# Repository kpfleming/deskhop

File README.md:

#  DeskHop - Fast Desktop Switching
## JLCPCB version (see below)

Did you ever notice how, in the crazy world of tech, there's always that one quirky little project trying to solve a problem so niche that its only competitors might be a left-handed screwdriver and a self-hiding alarm clock?

I use two different computers in my daily workflow and share a single keyboard/mouse pair between them. Trying several USB switching boxes found on Amazon made me realize they all suffer from similar issues - it takes a while to switch, the process is quite clumsy when trying to find the button and frankly, it just doesn't get any better with time. 

All I wanted was a way to use a keyboard shortcut to quickly switch outputs, paired with the ability to do the same by magically moving the mouse pointer between monitors. This project enables you to do both, even if your computers run different operating systems!

## Features

- Completely **free and open source**
- No noticeable delay when switching
- Simply drag the mouse pointer between computers
- No software installed
- Affordable and obtainable components (<15€)
- 3D printable snap-fit case
- Full Galvanic isolation between your outputs
- Works with Linux, macOS and Windows

------

## How it works

The device acts as an intermediary between your keyboard/mouse and the computer, establishing and maintaining connections with both computers at once. Then it chooses where to forward your mouse and keystrokes to, depending on your selection. Keyboard follows the mouse and vice versa, so just dragging the mouse to the other desktop will switch both.

## Mouse 

To get the mouse cursor to magically jump across, the mouse hid report descriptor was changed to use absolute coordinates and then the mouse reports (that still come in relative movements) accumulate internally, keeping the accurate tally on the position. 

When you try to leave the monitor area in the direction of the other monitor, it keeps the Y coordinate and swaps the maximum X for a minimum X, then flips the outputs. This ensures that the cursor seamlessly appears at the same height on the other monitor, enhancing the perception of a smooth transition.

 <p align="center"> Dragging the mouse from Mac to Linux automatically switches outputs. 
 </p>

-----
 
The actual switch happens at the very moment when one arrow stops moving and the other one starts.

## Keyboard

Acting as a USB Host and querying your keyboard periodically, it looks for a preconfigured hotkey in the hid report (usually Caps Lock for me). When found, it will forward all subsequent characters to the other output.

To have a visual indication which output you are using at any given moment, you can repurpose keyboard LEDs and have them provide the necessary feedback. 

It also remembers the LED state for each computer, so you can pick up exactly how you left it. 

## How to build

```
PICO_BOARD=pico PICO_SDK_PATH=/your/sdk/path cmake -S . -B build
cmake --build build
```

## Using pre-built images

Alternatively, you can use the [pre-built images](binaries/). Take the Pico board that goes to slot A on the PCB and hold the on-board button while connecting the cable.

It should appear as a USB drive on your system. Copy the corresponding board_A.uf2 file there and repeat the same with B.

## Upgrading firmware

Option 1 - Open the case, hold the button while connecting each Pico and copy the right uf2 to it.

Option 2 - Switch a board to BOOTSEL mode by using a special key combination (listed below). 

This will make the corresponding Pico board enter the bootloader upgrade mode and act as USB flash drive. Now you can drag-and-drop the .uf2 file to it (you might need to plug in your mouse directly).

## Misc features

### Mouse slowdown

Ever tried to move that YT video slider to a specific position but your mouse moves too jumpy and suddenly you are moving your hand super-carefully like you're 5 and playing "Operation" all over again?

**Press right CTRL + right ALT** to toggle a slow-mouse mode. The mouse pointer will slow down considerably, enabling you to get the finer precision work done and still have your mouse moving normally by quickly pressing the same keys again.

### Switch Lock

If you want to lock yourself to one screen, use ```RIGHT CTRL + L```.
This will make sure you won't accidentally leave your current screen. To turn off, press the same key combo again.

### Screensaver

Supposedly built in to prevent computer from entering standby, but truth be told - it is just fun to watch. Off by default, will make your mouse pointer bounce around the screen like a Pong ball. When enabled, it activates after a period of inactivity defined in user config header and automatically switches off as soon as you send any output towards that screen. 

## Hardware

[The circuit](schematics/DeskHop.pdf) is based on two Raspberry Pi Pico boards, chosen because they are cheap (4.10 € / pc), can be hand soldered and most suppliers have them in stock.

The Picos are connected using UART and separated by an Analog Devices ADuM1201 dual-channel digital isolator (~3€). 

While they normally don't have support for dual USB, thanks to an [amazing project](https://github.com/sekigon-gonnoc/Pico-PIO-USB) where USB is implemented using the programmable IO wizardry found in RP2040, there is support for it to act both as an USB host and device.  

## PCB

To keep things as simple as possible for DIY builds, the traces were kept on one side and the number of parts kept to a theoretical minimum.

USB D+/D- differential lines should be identical in length, but they are slightly asymmetrical on purpose to counter the length difference on the corresponding GPIO traces PICO PCB itself, so the overall lengths should match.

Zd (differential impedance) is aimed as 90 ohm (managed to get ~107, close enough :)).

The thickness is designed to be 1.6 mm for snap-fit to work as expected.

Planned changes:
- Add 15 ohm resistors for D+ / D- lines
- Add decoupling capacitance near VBUS line on USB-A connector (~100 uF)
- Add an ESD protection device near the USB connector
- Add indications on the silkscreen for pin1 on the ADuM1201
- Add indications on the silkscreen for which Raspberry Pi Pico pins need to be soldered

... done, waiting on PCBs to re-test and verify everything. Stay tuned for an updated version!

## Case

Since I'm not very good with 3d, the case is [simple and basic](case/) but does the job. It should be easy to print, uses ~33g of filament and takes a couple of hours.

Horizontal PCB movements are countered by pegs sliding through holes and vertical movements by snap-fit lugs on the side - no screws required.

Micro USB connectors on both boards are offset from the side of the case, so slightly larger holes should allow for cables to reach in. 

The lid is of a snap-fit design, with a screwdriver slot for opening. The markings on top are recessed and can be finished with e.g. crayons to give better contrast (or simply left as-is).

## Bill of materials

Note that this fork of the project has been converted to use parts
from [LCSC](https://www.lcsc.com/), specifically parts that are kept
in stock at JLCPCB. This reduces costs and shortens assembly times,
but is only useful if you plan on ordering fully-assembled boards from
JLCPCB.

Prices quoted below are from a qty 10 unit order on 2024-02-26.

| Component          | Qty | LCSC SKU | Unit Price / $ | Price / $|
|--------------------|-----|----------|----------------|----------|
| Raspberry Pi Pico  | 2   | C7203002 | 5.93           | 11.85    |
| ISO7721DRRZ        | 1   | C366164  | 0.56           |  0.56    |
| Cap 1206 SMD 100nF | 2   | C2858367 | 0.013          |  0.03    |
| USB-A PCB conn.    | 2   | C42411   | 0.049          |  0.10    |
| Headers 2.54 1x03  | 2   | C2915006 | 0.176          |  0.35    |
|                    |     |          |                |          |
|                    |     |          |          Total | 12.89    |

Additional steps:

 - making the PCB ([Gerber provided](pcb/), choose 1.6 mm thickness)
 - 3d printing the case ([stl files provided](case/), ~33g filament)

## Assembly guide

If you have some experience with electronics, you don't need this. However, some of you might not, and in that case this video might help guide you through the process. Please note, after soldering you should clean the flux from the PCB to prevent corrosion. 

The standard process to do that is using isopropyl alcohol and an old toothbrush. But guess what? I'm not putting my old toothbrush online, so you'll just have to improvise that part :)

## Usage guide

### Keyboard shortcuts

_Firmware upgrade_
- ```Right Shift + F12 + Left Shift + A``` - put board A in FW upgrade mode
- ```Right Shift + F12 + Left Shift + B``` - put board B in FW upgrade mode

_Usage_
- ```Right CTRL + Right ALT``` - Toggle slower mouse mode
- ```Right CTRL + L``` - Lock/Unlock mouse desktop switching
- ```Caps Lock``` - Switch between outputs

_Config_
- ```Right Shift + F12 + D``` - remove flash config
- ```Right Shift + F12 + Y``` - save screen switch offset
- ```Right Shift + F12 + S``` - turn on/off screensaver option

### Switch cursor height calibration

This step is not required, but it can be handy if your screens are not perfectly aligned or differ in size. The objective is to have the mouse pointer come out at exactly the same height.

Just park your mouse on the LARGER screen at the height of the smaller/lower screen (illustrated) and press ```Right Shift + F12 + Y```. Your LED (and caps lock) should flash in confirmation.

Repeat for the bottom border (if it's above the larger screen's border). This will get saved to flash and it should keep this calibration value from now on.

### Other configuration

Mouse speed can now be configured per output screen and per axis. If you have multiple displays under Linux, your X speed is probably too fast, so you need to configure it in user_config.h and rebuild. In the future, this will be configurable without having to do that.

### Functional verification

When you connect a new USB peripheral, the board will flash the led twice, and instruct the other board to do the same. This way you can test if USB and outgoing communication works for each board.

Do this test by first plugging the keyboard on one side and then on the other. If everything is OK, leds will flash quickly back and forth in both cases.

## Security and Safety

Some features are missing on purpose, despite the fact it would make the device easier to use or simpler to configure. Here is a quick breakdown of these decisions:

- There is no copy-paste or *any* information sharing between systems. This prevents information leakage.
- No webhid device management or any inbound connectivity from the output computers, with the only exception of standard keyboard LED on/off messages, hard limited to 1 byte of data.
- No FW upgrade triggering from the outputs. Only explicit and deliberate user action through a special keyboard shortcut may do that.
- No plugged-in keyboard/mouse custom endpoints are exposed or information forwarded towards these devices. Their potential vulnerabilities are effectively firewalled from the computer.
- No input history is allowed to be retained.
- Outputs are physically separated and galvanically isolated with a minimal isolation voltage of 2kV.
- All packets exchanged between devices are of fixed length, no code is transferred and no raw config exchange of any kind can take place.
- There is no bluetooth or wifi, networking, Internet access, usb drives etc.
- No connected computer is considered trusted under any circumstances.
- Entirety of the code is open source, without any binary blobs and thoroughly commented to explain its purpose. I encourage you to never trust anyone and always make sure you know what you are running by doing a manual audit.

This still doesn't guarantee anything, but I believe it makes a reasonable set of ground rules to keep you safe and protected.

## FAQ

1. I just have two Picos, can I do without a PCB and isolator?

*Sure. Having an isolator is recommended but it should work without it.*

2. What happens if I have two different resolutions on my monitors?

*The mouse movement is done in abstract coordinate space and your computer figures out how that corresponds with the physical screen, so it should just work.*

3. Where can I buy it?

*I'm not selling anything, this is just a personal, non-commercial hobby project.*

*[update] There is a manufacturing/assembly company in China that might offer PCBs in qty of 1, assembled boards and boards + case, so stay tuned.*

*I **don't want to take any commission** on this - the only goal is to provide an alternative for people who don't feel confident enough to assemble the boards themselves.*

4. When the active screen is changed via the mouse, does the keyboard follow (and vice versa)?

*Yes, the idea was to make it behave like it was one single computer.*

5. Will this work with keyboard/mouse combo dongles, like the Logitech Unifying receiver?

*Not tested yet, but the latest version might actually work (please provide feedback).*

6. Will this work with wireless mice and keyboards that have separate wireless receivers (one for the mouse, another for the keyboard)?

*It should work - tried an Anker wireless mouse with a separate receiver and that worked just fine.*

7. I have issues with build or compilation

*Check out the [Troubleshooting Wiki](https://github.com/hrvach/deskhop/wiki/Troubleshooting) that might have some answers.*

## Software Alternatives

There are several software alternatives you can use if that works in your particular situation.

1. [Barrier](https://github.com/debauchee/barrier) - Free, Open Source
2. [Input Leap](https://github.com/input-leap/input-leap) - Free, Open Source
3. [Synergy](https://symless.com/synergy) - Commercial
4. [Mouse Without Borders](https://www.microsoft.com/en-us/garage/wall-of-fame/mouse-without-borders/) - Free, Windows only
5. [Universal Control](https://support.apple.com/en-my/HT212757) - Free, Apple thing

## Shortcomings

- Windows 10 broke HID absolute coordinates behavior in KB5003637, so you can't use more than 1 screen on Windows (mouse will stay on the main screen).
- Code needs cleanup, some refactoring etc.
- Occasional bugs and weird behavior.
- Not tested with a wide variety of devices, I don't know how it will work with your hardware. There is a reasonable chance things might not work out-of-the-box. 
- Advanced keyboards (with knobs, extra buttons or sliders) will probably face issues where this additional hardware doesn't work.
- Super-modern mice with 300 buttons might see some buttons not work as expected.
- NOTE: Both computers need to be connected and provide power to the USB for this to work (as each board gets powered by the computer it plugs into). Many desktops and laptops will provide power even when shut down nowadays. If you need to run with one board fully disconnected, you should be able to use a USB hub to plug both keyboard and mouse to a single port.

## Progress

So, what's the deal with all the enthusiasm? I can't believe it - please allow me to thank you all! I've never expected this kind of interest in a simple personal project, so the initial features are pretty basic (just like my cooking skills) and mostly cover my own usecase. Stay tuned for firmware updates that should bring wider device compatibility, more features and less bugs. As this is a hobby project, I appreciate your understanding for being time-constrained and promise to do the best I can.

Planned features:
- ~~Proper TinyUSB host integration~~ (done)
- ~~HID report protocol parsing, not just boot protocol~~ (mostly done)
- ~~Support for unified dongle receivers~~
- ~~Support for USB hubs and single-sided operation~~
- Configurable screens (partially)
- ~~Permament configuration stored in flash~~
- Better support for keyboards with knobs and mice with mickeys
- Unified firmware for both Picos
- ... and more!

Working on a *lite* version which provides basic functionality with just a single Pico W board, lowering the cost even further and enabling you to try it out even with no added hardware or PCB.

Mouse polling should now work at 1000 Hz (the dips in the graph is my arm hurting from all the movement :-)):

## Disclaimer

I kindly request that anyone attempting to build this project understands and acknowledges that I am not liable for any injuries, damages, or other consequences. Your safety is important, and I encourage you to approach this project carefully, taking necessary precautions and assuming personal responsibility for your well-being throughout the process. Please don't get electrocuted, burned, stressed or angry. Have fun and enjoy! 

Happy switchin'!

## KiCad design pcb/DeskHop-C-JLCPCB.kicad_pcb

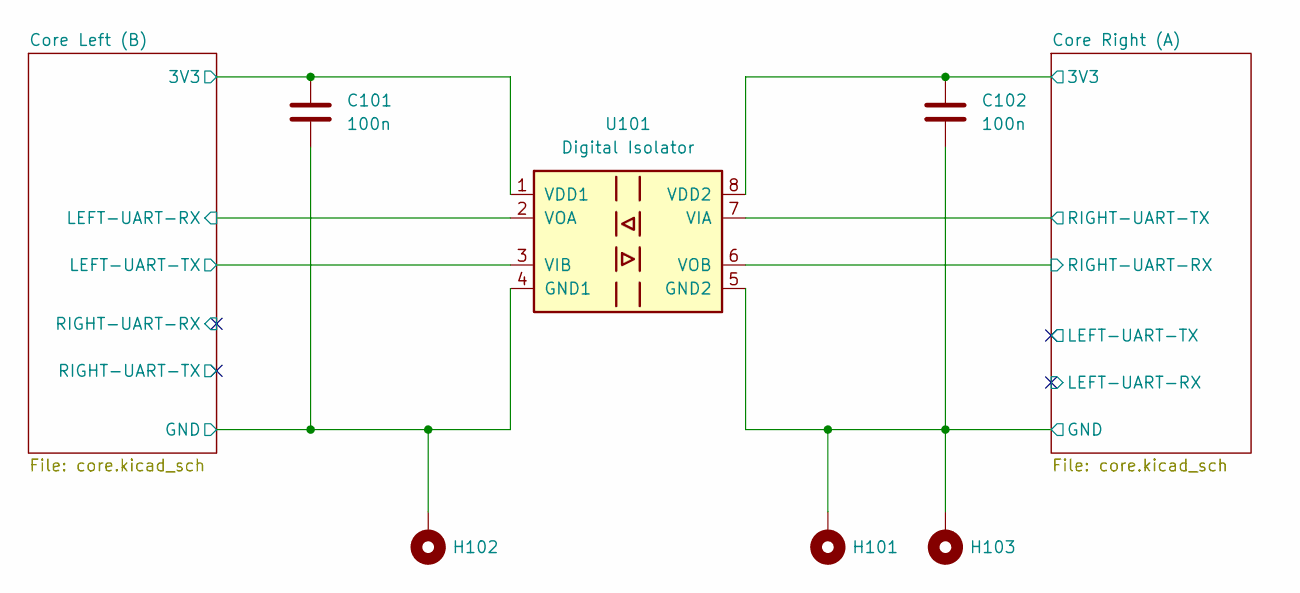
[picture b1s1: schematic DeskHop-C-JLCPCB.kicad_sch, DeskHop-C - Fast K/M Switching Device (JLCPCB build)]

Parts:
C101, C102: 100n; C_0402_1005Metric; MPN CC0402KRX5R5BB104; LCSC C541405
H101, H102, H103: MountingHole_Pad; MountingHole_2.7mm_M2.5_Pad_Via
U101: Digital Isolator; SOIC-8_3.9x4.9mm_P1.27mm; MPN ISO7721DR; LCSC C366164

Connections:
/Core Left (B)/3V3: C101.1, U101.1 (VDD1); also elsewhere on the board
/Core Left (B)/GND: C101.2, H102.1, U101.4 (GND1); also elsewhere on the board
/Core Left (B)/LEFT-UART-RX: U101.2 (VOA); also elsewhere on the board
/Core Left (B)/LEFT-UART-TX: U101.3 (VIB); also elsewhere on the board
/Core Right (A)/3V3: C102.1, U101.8 (VDD2); also elsewhere on the board
/Core Right (A)/GND: C102.2, H101.1, H103.1, U101.5 (GND2); also elsewhere on the board
/Core Right (A)/RIGHT-UART-RX: U101.6 (VOB); also elsewhere on the board
/Core Right (A)/RIGHT-UART-TX: U101.7 (VIA); also elsewhere on the board

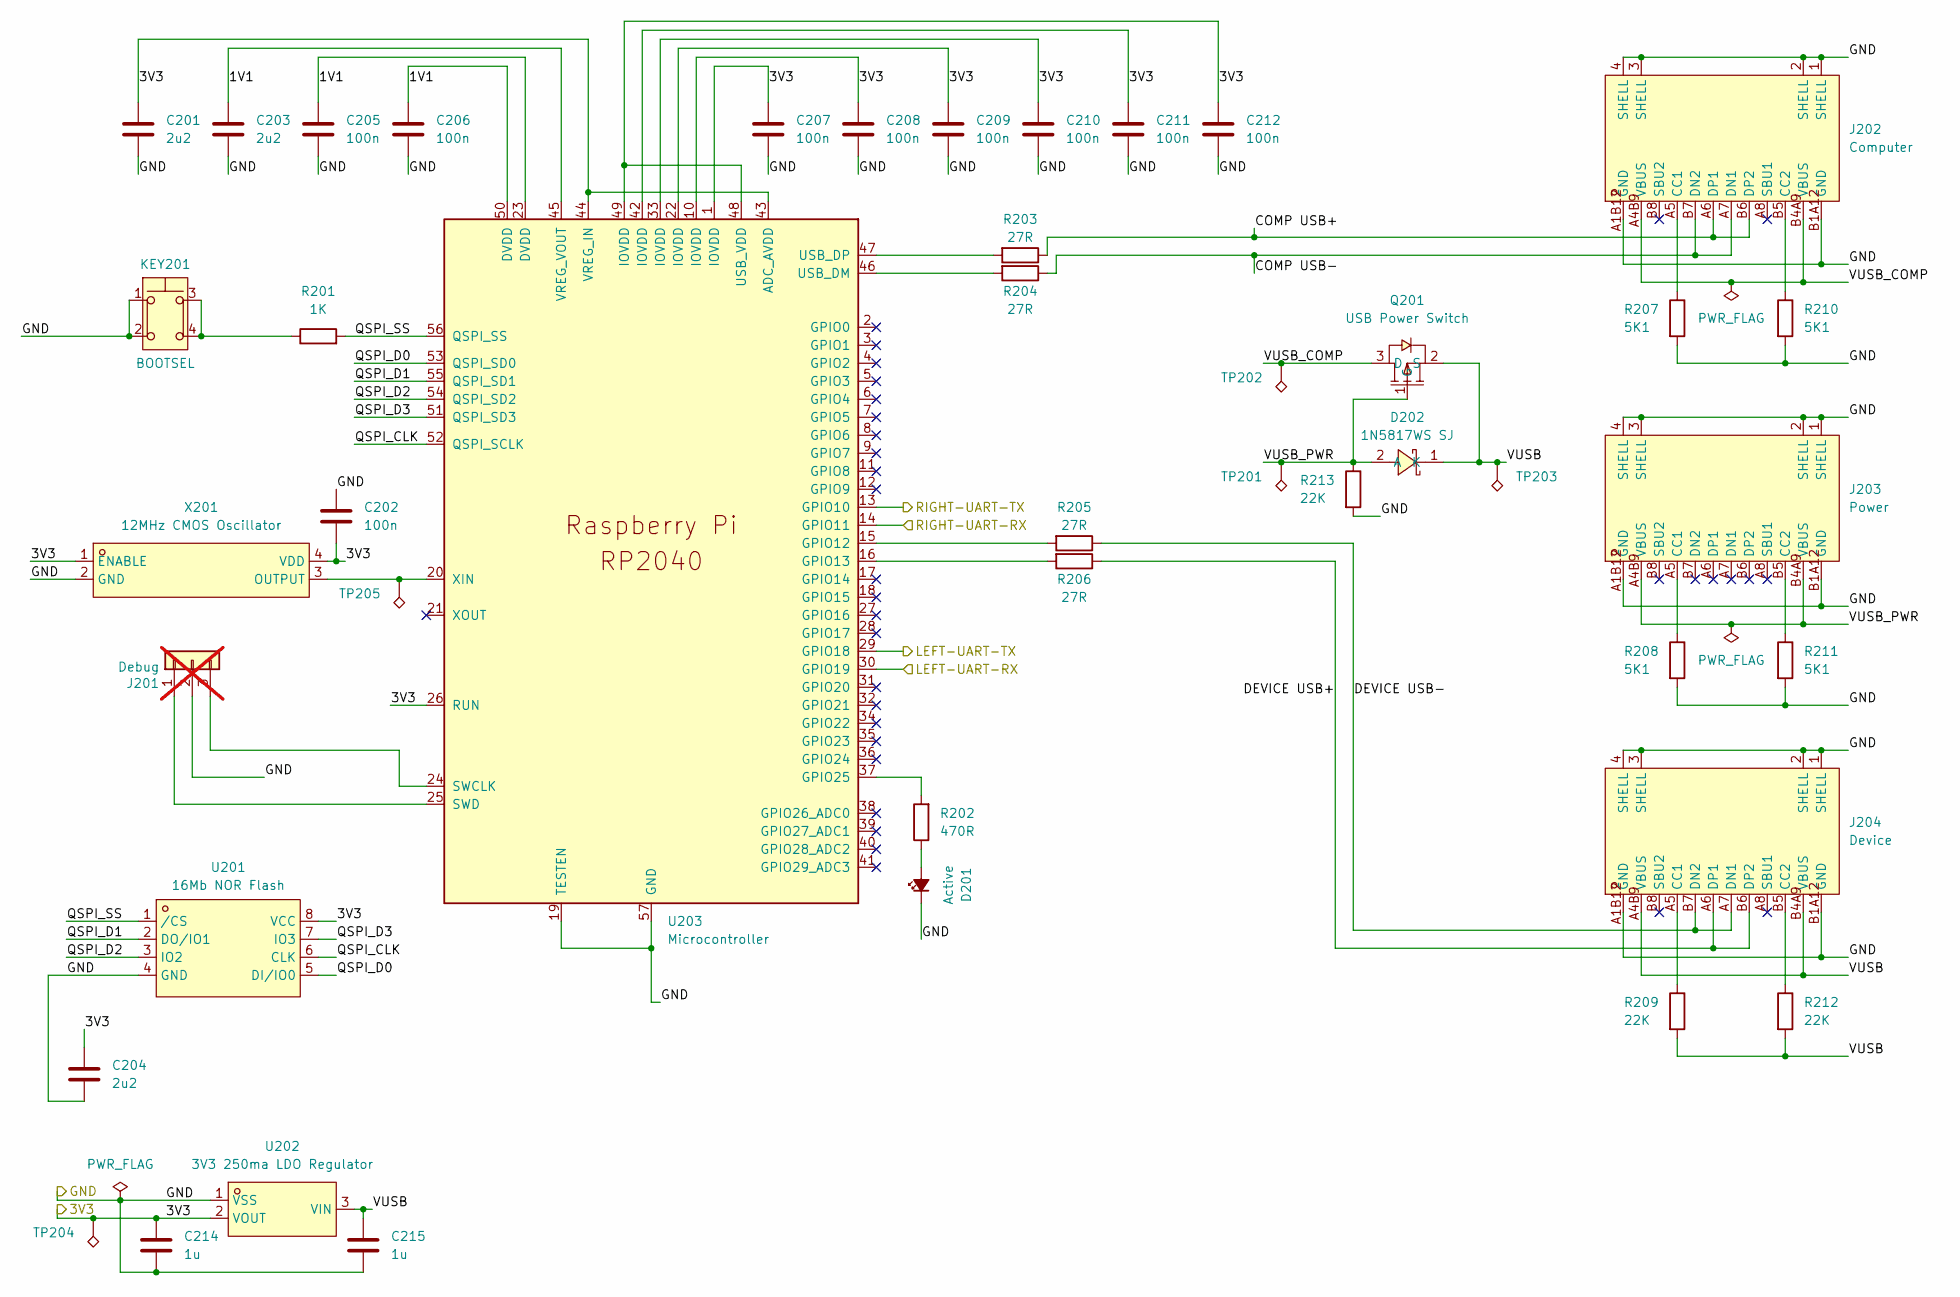
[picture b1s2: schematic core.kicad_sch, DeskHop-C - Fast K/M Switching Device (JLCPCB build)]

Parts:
C201, C203, C204: 2u2; C_0402_1005Metric; MPN CC0402KRX5R5BB225; LCSC C541409
C202, C205, C206, C207, C208, C209, C210, C211, C212: 100n; C_0402_1005Metric; MPN CC0402KRX5R5BB104; LCSC C541405
C214, C215: 1u; C_0402_1005Metric; MPN CC0402KRX5R5BB105; LCSC C106253
D201: Active; LED_0603_1608Metric; MPN NCD0805B2APG1608CGKC/T; LCSC C5875737
D202: 1N5817WS SJ; SOD-323_L1.7-W1.3-LS2.6-RD-1; MPN 1N5817WS; LCSC C2828424
J201: Debug; PinHeader_1x03_P2.54mm_Vertical; not fitted
J202: Computer; USB-C-SMD_G-SWITCH_GT-USB-7010ASV; MPN GT-USB-7010ASV; LCSC C2988369
J203: Power; USB-C-SMD_G-SWITCH_GT-USB-7010ASV; MPN GT-USB-7010ASV; LCSC C2988369
J204: Device; USB-C-SMD_G-SWITCH_GT-USB-7010ASV; MPN GT-USB-7010ASV; LCSC C2988369
KEY201: BOOTSEL; KEY-SMD_4P-L4.2-W3.2-P2.20-LS4.6; MPN SKRPASE010; LCSC C470427
Q201: USB Power Switch; SOT-23-3_L2.9-W1.3-P0.95-LS2.4-BR-1; MPN DMG2305UX; LCSC C2940629
R201: 1K; R_0402_1005Metric; MPN AC0402FR-071KL; LCSC C144789
R202: 470R; R_0402_1005Metric; MPN AC0402FR-07470RL; LCSC C227095
R203, R204, R205, R206: 27R; R_0402_1005Metric; MPN RC0402FR-0727RL; LCSC C138021
R207, R208, R210, R211: 5K1; R_0402_1005Metric; MPN AC0402FR-075K1L; LCSC C144745
R209, R212, R213: 22K; R_0402_1005Metric; MPN AC0402FR-0722KL; LCSC C144778
TP201, TP202, TP203, TP204, TP205: TestPoint_Alt; TestPoint_Pad_1.0x1.0mm
U201: 16Mb NOR Flash; SOIC-8_L5.3-W5.3-P1.27-LS8.0-BL; MPN W25Q16JVSSIQ; LCSC C82317
U202: 3V3 250ma LDO Regulator; SOT-23-3_L3.0-W1.7-P0.95-LS2.9-BR; MPN XC6206P332MR; LCSC C347376
U203: Microcontroller; RP2040-QFN-56; MPN RP2040; LCSC C2040
X201: 12MHz CMOS Oscillator; OSC-SMD_4P-L3.2-W2.5-BL-1; MPN S3D12.000000B20F30T; LCSC C387348

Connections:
/Core Left (B)/1V1: C203.2, C205.2, C206.2, U203.23 (DVDD), U203.45 (VREG_VOUT), U203.50 (DVDD)
/Core Left (B)/3V3: C201.2, C202.1, C204.1, C207.2, C208.2, C209.2, C210.2, C211.2, C212.2, C214.1, TP204.1, U201.8 (VCC), U202.2 (VOUT), U203.1 (IOVDD), U203.10 (IOVDD), U203.22 (IOVDD), U203.26 (RUN), U203.33 (IOVDD), U203.42 (IOVDD), U203.43 (ADC_AVDD), U203.44 (VREG_IN), U203.48 (USB_VDD), U203.49 (IOVDD), X201.1 (ENABLE), X201.4 (VDD); also elsewhere on the board
/Core Left (B)/COMP USB+: J202.A6 (DP1), J202.B6 (DP2), R203.1
/Core Left (B)/COMP USB-: J202.A7 (DN1), J202.B7 (DN2), R204.1
/Core Left (B)/DEVICE USB+: J204.A6 (DP1), J204.B6 (DP2), R205.1
/Core Left (B)/DEVICE USB-: J204.A7 (DN1), J204.B7 (DN2), R206.1
/Core Left (B)/GND: C201.1, C202.2, C203.1, C204.2, C205.1, C206.1, C207.1, C208.1, C209.1, C210.1, C211.1, C212.1, C214.2, C215.2, D201.1 (K), J201.2, J202.1 (SHELL), J202.2 (SHELL), J202.3 (SHELL), J202.4 (SHELL), J202.A1B12 (GND), J202.B1A12 (GND), J203.1 (SHELL), J203.2 (SHELL), J203.3 (SHELL), J203.4 (SHELL), J203.A1B12 (GND), J203.B1A12 (GND), J204.1 (SHELL), J204.2 (SHELL), J204.3 (SHELL), J204.4 (SHELL), J204.A1B12 (GND), J204.B1A12 (GND), KEY201.1, KEY201.2, R207.2, R208.2, R210.2, R211.2, R213.2, U201.4 (GND), U202.1 (VSS), U203.19 (TESTEN), U203.57 (GND), X201.2 (GND); also elsewhere on the board
/Core Left (B)/LEFT-UART-RX: U203.30 (GPIO19); also elsewhere on the board
/Core Left (B)/LEFT-UART-TX: U203.29 (GPIO18); also elsewhere on the board
/Core Left (B)/QSPI_CLK: U201.6 (CLK), U203.52 (QSPI_SCLK)
/Core Left (B)/QSPI_D0: U201.5 (DI/IO0), U203.53 (QSPI_SD0)
/Core Left (B)/QSPI_D1: U201.2 (DO/IO1), U203.55 (QSPI_SD1)
/Core Left (B)/QSPI_D2: U201.3 (IO2), U203.54 (QSPI_SD2)
/Core Left (B)/QSPI_D3: U201.7 (IO3), U203.51 (QSPI_SD3)
/Core Left (B)/QSPI_SS: R201.2, U201.1 (/CS), U203.56 (QSPI_SS)
/Core Left (B)/RIGHT-UART-RX: U203.14 (GPIO11)
/Core Left (B)/RIGHT-UART-TX: U203.13 (GPIO10)
/Core Left (B)/VUSB: C215.1, D202.1 (K), J204.A4B9 (VBUS), J204.B4A9 (VBUS), Q201.2 (S), R209.2, R212.2, TP203.1, U202.3 (VIN)
/Core Left (B)/VUSB_COMP: J202.A4B9 (VBUS), J202.B4A9 (VBUS), Q201.3 (D), TP202.1
/Core Left (B)/VUSB_PWR: D202.2 (A), J203.A4B9 (VBUS), J203.B4A9 (VBUS), Q201.1 (G), R213.1, TP201.1
unnamed: D201.2 (A), R202.1
unnamed: J201.1, U203.25 (SWD)
unnamed: J201.3, U203.24 (SWCLK)
unnamed: J202.A5 (CC1), R207.1
unnamed: J202.B5 (CC2), R210.1
unnamed: J203.A5 (CC1), R208.1
unnamed: J203.B5 (CC2), R211.1
unnamed: J204.A5 (CC1), R209.1
unnamed: J204.B5 (CC2), R212.1
unnamed: KEY201.3, KEY201.4, R201.1
unnamed: R206.2, U203.15 (GPIO12)
unnamed: R205.2, U203.16 (GPIO13)
unnamed: R202.2, U203.37 (GPIO25)
unnamed: R204.2, U203.46 (USB_DM)
unnamed: R203.2, U203.47 (USB_DP)
unnamed: TP205.1, U203.20 (XIN), X201.3 (OUTPUT)

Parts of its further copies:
C301, C303, C304: 2u2; C_0402_1005Metric; MPN CC0402KRX5R5BB225; LCSC C541409
C302, C305, C306, C307, C308, C309, C310, C311, C312: 100n; C_0402_1005Metric; MPN CC0402KRX5R5BB104; LCSC C541405
C314, C315: 1u; C_0402_1005Metric; MPN CC0402KRX5R5BB105; LCSC C106253
D301: Active; LED_0603_1608Metric; MPN NCD0805B2APG1608CGKC/T; LCSC C5875737
D302: 1N5817WS SJ; SOD-323_L1.7-W1.3-LS2.6-RD-1; MPN 1N5817WS; LCSC C2828424
J301: Debug; PinHeader_1x03_P2.54mm_Vertical; not fitted
J302: Computer; USB-C-SMD_G-SWITCH_GT-USB-7010ASV; MPN GT-USB-7010ASV; LCSC C2988369
J303: Power; USB-C-SMD_G-SWITCH_GT-USB-7010ASV; MPN GT-USB-7010ASV; LCSC C2988369
J304: Device; USB-C-SMD_G-SWITCH_GT-USB-7010ASV; MPN GT-USB-7010ASV; LCSC C2988369
KEY301: BOOTSEL; KEY-SMD_4P-L4.2-W3.2-P2.20-LS4.6; MPN SKRPASE010; LCSC C470427
Q301: USB Power Switch; SOT-23-3_L2.9-W1.3-P0.95-LS2.4-BR-1; MPN DMG2305UX; LCSC C2940629
R301: 1K; R_0402_1005Metric; MPN AC0402FR-071KL; LCSC C144789
R302: 470R; R_0402_1005Metric; MPN AC0402FR-07470RL; LCSC C227095
R303, R304, R305, R306: 27R; R_0402_1005Metric; MPN RC0402FR-0727RL; LCSC C138021
R307, R308, R310, R311: 5K1; R_0402_1005Metric; MPN AC0402FR-075K1L; LCSC C144745
R309, R312, R313: 22K; R_0402_1005Metric; MPN AC0402FR-0722KL; LCSC C144778
TP301, TP302, TP303, TP304, TP305: TestPoint_Alt; TestPoint_Pad_1.0x1.0mm
U301: 16Mb NOR Flash; SOIC-8_L5.3-W5.3-P1.27-LS8.0-BL; MPN W25Q16JVSSIQ; LCSC C82317
U302: 3V3 250ma LDO Regulator; SOT-23-3_L3.0-W1.7-P0.95-LS2.9-BR; MPN XC6206P332MR; LCSC C347376
U303: Microcontroller; RP2040-QFN-56; MPN RP2040; LCSC C2040
X301: 12MHz CMOS Oscillator; OSC-SMD_4P-L3.2-W2.5-BL-1; MPN S3D12.000000B20F30T; LCSC C387348

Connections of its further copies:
/Core Right (A)/1V1: C303.2, C305.2, C306.2, U303.23 (DVDD), U303.45 (VREG_VOUT), U303.50 (DVDD)
/Core Right (A)/3V3: C301.2, C302.1, C304.1, C307.2, C308.2, C309.2, C310.2, C311.2, C312.2, C314.1, TP304.1, U301.8 (VCC), U302.2 (VOUT), U303.1 (IOVDD), U303.10 (IOVDD), U303.22 (IOVDD), U303.26 (RUN), U303.33 (IOVDD), U303.42 (IOVDD), U303.43 (ADC_AVDD), U303.44 (VREG_IN), U303.48 (USB_VDD), U303.49 (IOVDD), X301.1 (ENABLE), X301.4 (VDD); also elsewhere on the board
/Core Right (A)/COMP USB+: J302.A6 (DP1), J302.B6 (DP2), R303.1
/Core Right (A)/COMP USB-: J302.A7 (DN1), J302.B7 (DN2), R304.1
/Core Right (A)/DEVICE USB+: J304.A6 (DP1), J304.B6 (DP2), R305.1
/Core Right (A)/DEVICE USB-: J304.A7 (DN1), J304.B7 (DN2), R306.1
/Core Right (A)/GND: C301.1, C302.2, C303.1, C304.2, C305.1, C306.1, C307.1, C308.1, C309.1, C310.1, C311.1, C312.1, C314.2, C315.2, D301.1 (K), J301.2, J302.1 (SHELL), J302.2 (SHELL), J302.3 (SHELL), J302.4 (SHELL), J302.A1B12 (GND), J302.B1A12 (GND), J303.1 (SHELL), J303.2 (SHELL), J303.3 (SHELL), J303.4 (SHELL), J303.A1B12 (GND), J303.B1A12 (GND), J304.1 (SHELL), J304.2 (SHELL), J304.3 (SHELL), J304.4 (SHELL), J304.A1B12 (GND), J304.B1A12 (GND), KEY301.1, KEY301.2, R307.2, R308.2, R310.2, R311.2, R313.2, U301.4 (GND), U302.1 (VSS), U303.19 (TESTEN), U303.57 (GND), X301.2 (GND); also elsewhere on the board
/Core Right (A)/LEFT-UART-RX: U303.30 (GPIO19)
/Core Right (A)/LEFT-UART-TX: U303.29 (GPIO18)
/Core Right (A)/QSPI_CLK: U301.6 (CLK), U303.52 (QSPI_SCLK)
/Core Right (A)/QSPI_D0: U301.5 (DI/IO0), U303.53 (QSPI_SD0)
/Core Right (A)/QSPI_D1: U301.2 (DO/IO1), U303.55 (QSPI_SD1)
/Core Right (A)/QSPI_D2: U301.3 (IO2), U303.54 (QSPI_SD2)
/Core Right (A)/QSPI_D3: U301.7 (IO3), U303.51 (QSPI_SD3)
/Core Right (A)/QSPI_SS: R301.2, U301.1 (/CS), U303.56 (QSPI_SS)
/Core Right (A)/RIGHT-UART-RX: U303.14 (GPIO11); also elsewhere on the board
/Core Right (A)/RIGHT-UART-TX: U303.13 (GPIO10); also elsewhere on the board
/Core Right (A)/VUSB: C315.1, D302.1 (K), J304.A4B9 (VBUS), J304.B4A9 (VBUS), Q301.2 (S), R309.2, R312.2, TP303.1, U302.3 (VIN)
/Core Right (A)/VUSB_COMP: J302.A4B9 (VBUS), J302.B4A9 (VBUS), Q301.3 (D), TP302.1
/Core Right (A)/VUSB_PWR: D302.2 (A), J303.A4B9 (VBUS), J303.B4A9 (VBUS), Q301.1 (G), R313.1, TP301.1
unnamed: D301.2 (A), R302.1
unnamed: J301.1, U303.25 (SWD)
unnamed: J301.3, U303.24 (SWCLK)
unnamed: J302.A5 (CC1), R307.1
unnamed: J302.B5 (CC2), R310.1
unnamed: J303.A5 (CC1), R308.1
unnamed: J303.B5 (CC2), R311.1
unnamed: J304.A5 (CC1), R309.1
unnamed: J304.B5 (CC2), R312.1
unnamed: KEY301.3, KEY301.4, R301.1
unnamed: R306.2, U303.15 (GPIO12)
unnamed: R305.2, U303.16 (GPIO13)
unnamed: R302.2, U303.37 (GPIO25)
unnamed: R304.2, U303.46 (USB_DM)
unnamed: R303.2, U303.47 (USB_DP)
unnamed: TP305.1, U303.20 (XIN), X301.3 (OUTPUT)

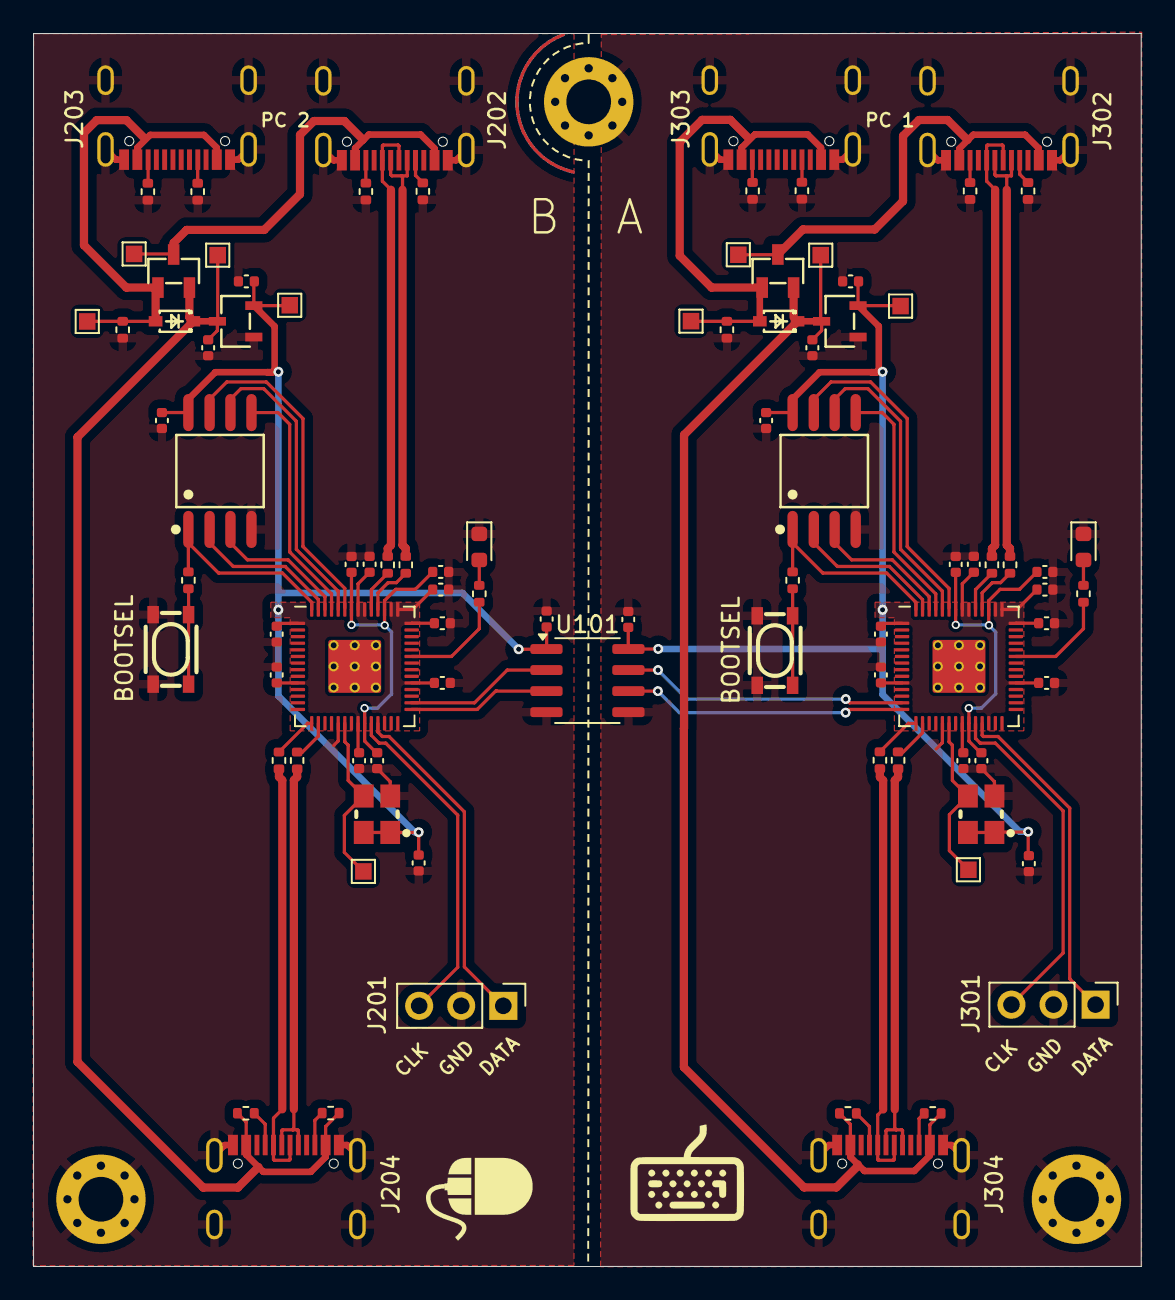
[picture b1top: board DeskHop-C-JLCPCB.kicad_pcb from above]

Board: 2 copper layers, 66.9 x 74.5 mm, 94 parts (0 on the bottom side), 68 nets.

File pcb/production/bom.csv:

Designator,Footprint,Quantity,Value,LCSC Part #
"C101, C102, C202, C205, C206, C207, C208, C209, C210, C211, C212, C302, C305, C306, C307, C308, C309, C310, C311, C312",0402,20,100n,C541405
"C201, C203, C204, C301, C303, C304",0402,6,2u2,C541409
"C214, C215, C314, C315",0402,4,1u,C106253
"D201, D301",0603,2,Active,C5875737
"D202, D302",SOD-323_L1.7-W1.3-LS2.6-RD-1,2,1N5817WS SJ,C2828424
"J202, J302",USB-C-SMD_G-SWITCH_GT-USB-7010ASV,2,Computer,C2988369
"J203, J303",USB-C-SMD_G-SWITCH_GT-USB-7010ASV,2,Power,C2988369
"J204, J304",USB-C-SMD_G-SWITCH_GT-USB-7010ASV,2,Device,C2988369
"KEY201, KEY301",KEY-SMD_4P-L4.2-W3.2-P2.20-LS4.6,2,BOOTSEL,C470427
"Q201, Q301",SOT-23-3_L2.9-W1.3-P0.95-LS2.4-BR-1,2,USB Power Switch,C2940629
"R201, R301",0402,2,1K,C144789
"R202, R302",0402,2,470R,C227095
"R203, R204, R205, R206, R303, R304, R305, R306",0402,8,27R,C138021
"R207, R208, R210, R211, R307, R308, R310, R311",0402,8,5K1,C144745
"R209, R212, R213, R309, R312, R313",0402,6,22K,C144778
U101,SOIC-8_3.9x4.9mm_P1.27mm,1,Digital Isolator,C366164
"U201, U301",SOIC-8_L5.3-W5.3-P1.27-LS8.0-BL,2,16Mb NOR Flash,C82317
"U202, U302",SOT-23-3_L3.0-W1.7-P0.95-LS2.9-BR,2,3V3 250ma LDO Regulator,C347376
"U203, U303",RP2040-QFN-56,2,Microcontroller,C2040
"X201, X301",OSC-SMD_4P-L3.2-W2.5-BL-1,2,12MHz CMOS Oscillator,C387348

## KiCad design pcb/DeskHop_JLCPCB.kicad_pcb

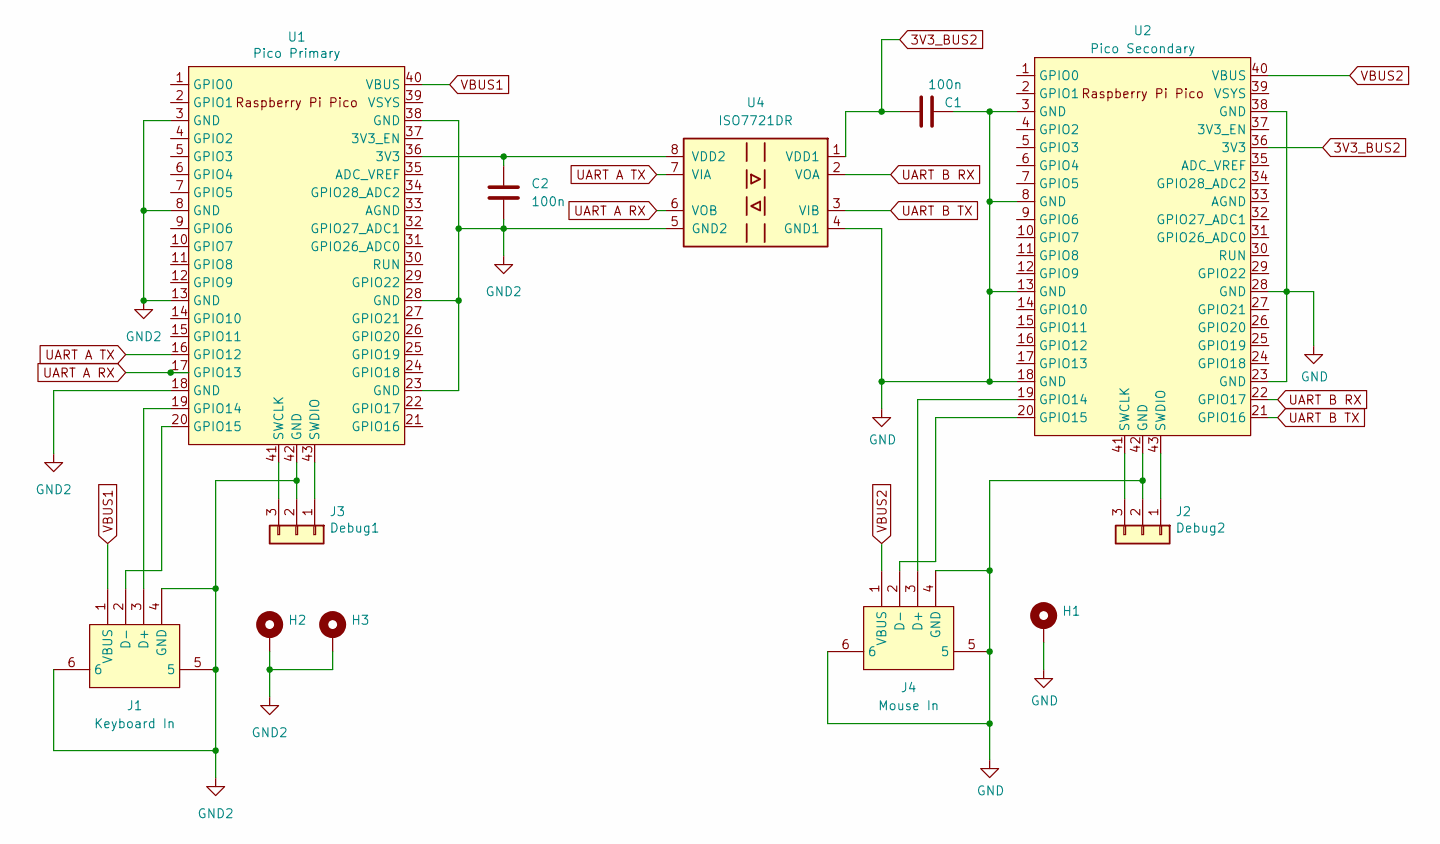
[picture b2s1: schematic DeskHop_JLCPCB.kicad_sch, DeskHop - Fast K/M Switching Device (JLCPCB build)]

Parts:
C1, C2: 100n; C_1206_3216Metric_Pad1.33x1.80mm_HandSolder; LCSC C2858367
H1, H2: MountingHole_Pad; MountingHole_2.7mm_M2.5_Pad_TopBottom
H3: MountingHole_Pad; MountingHole_2.7mm_M2.5_Pad_TopOnly
J1: Keyboard In; USB-A-TH_JTJ-USB-10.6-002; LCSC C42411
J2: Debug2; PinHeader_1x03_P2.54mm_Vertical; LCSC C2915006
J3: Debug1; PinHeader_1x03_P2.54mm_Vertical; LCSC C2915006
J4: Mouse In; USB-A-TH_JTJ-USB-10.6-002; LCSC C42411
U1: Pico Primary; RPi_Pico_SMD_Nohole; LCSC PICO
U2: Pico Secondary; RPi_Pico_SMD_Nohole; LCSC PICO
U4: ISO7721DR; SOIC-8_3.9x4.9mm_P1.27mm; LCSC C366164

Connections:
3V3_BUS2: C1.1, U2.36 (3V3), U4.1 (VDD1)
GND: C1.2, H1.1, J2.2, J4.4 (GND), J4.5, J4.6, U2.3 (GND), U2.8 (GND), U2.13 (GND), U2.18 (GND), U2.23 (GND), U2.28 (GND), U2.38 (GND), U2.42 (GND), U4.4 (GND1)
GND2: C2.2, H2.1, H3.1, J1.4 (GND), J1.5, J1.6, J3.2, U1.3 (GND), U1.8 (GND), U1.13 (GND), U1.18 (GND), U1.23 (GND), U1.28 (GND), U1.38 (GND), U1.42 (GND), U4.5 (GND2)
unnamed: J1.3 (D+), U1.19 (GPIO14)
unnamed: J1.2 (D-), U1.20 (GPIO15)
unnamed: J2.1, U2.43 (SWDIO)
unnamed: J2.3, U2.41 (SWCLK)
unnamed: J3.1, U1.43 (SWDIO)
unnamed: J3.3, U1.41 (SWCLK)
unnamed: J4.3 (D+), U2.19 (GPIO14)
unnamed: J4.2 (D-), U2.20 (GPIO15)
unnamed: C2.1, U1.36 (3V3), U4.8 (VDD2)
UART A RX: U1.17 (GPIO13), U4.6 (VOB)
UART A TX: U1.16 (GPIO12), U4.7 (VIA)
UART B RX: U2.22 (GPIO17), U4.2 (VOA)
UART B TX: U2.21 (GPIO16), U4.3 (VIB)
VBUS1: J1.1 (VBUS), U1.40 (VBUS)
VBUS2: J4.1 (VBUS), U2.40 (VBUS)

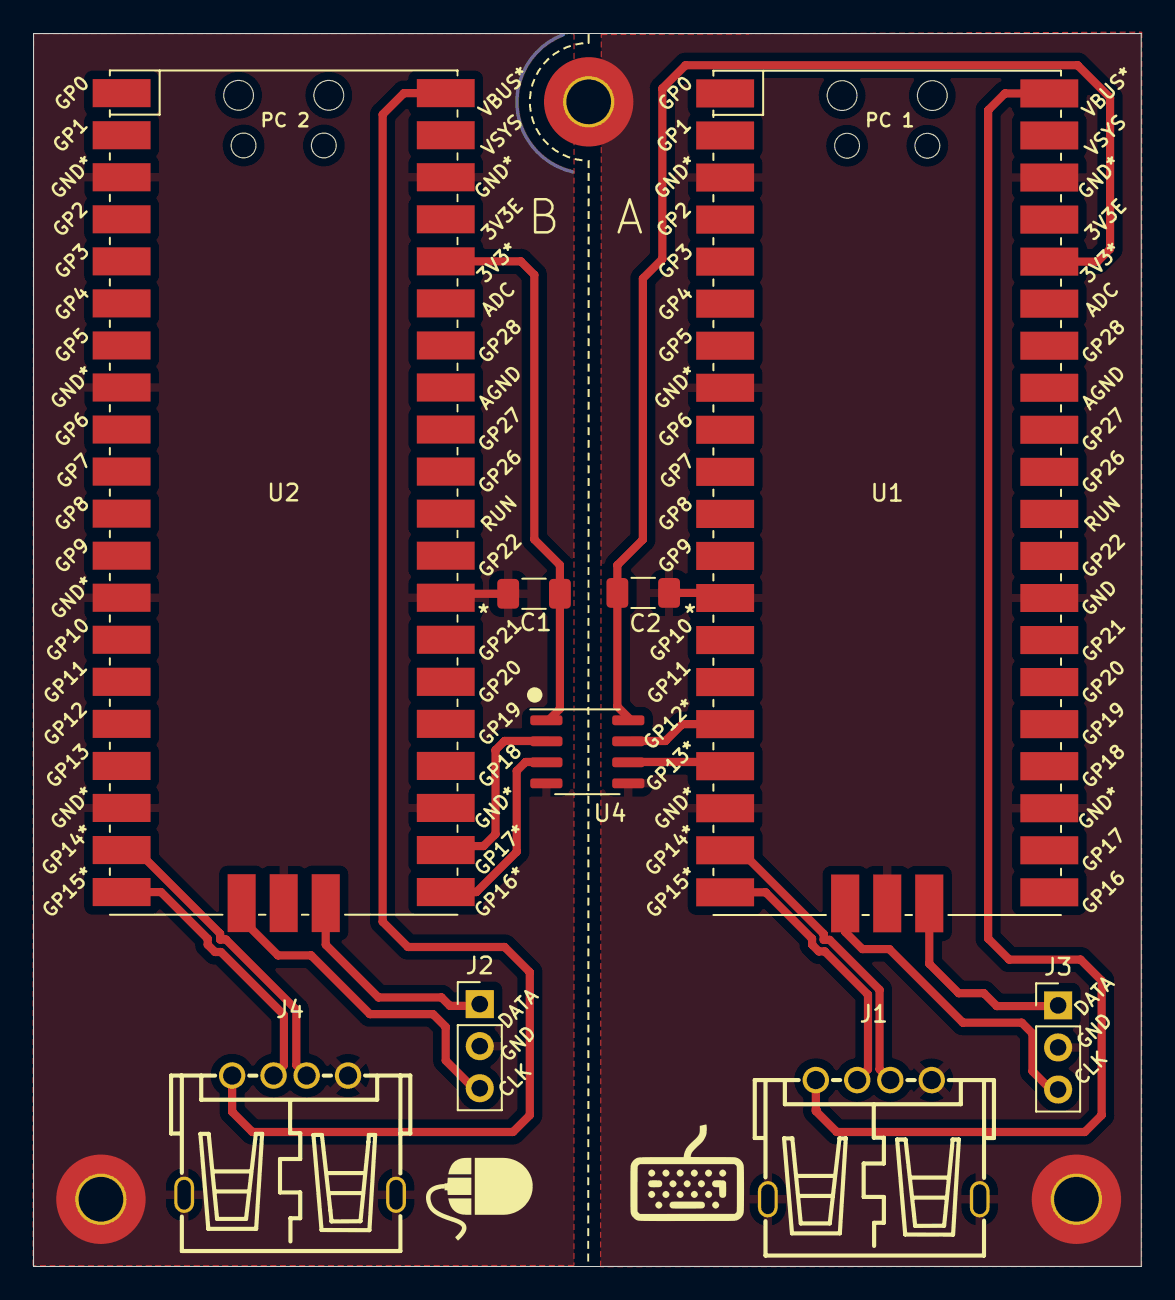
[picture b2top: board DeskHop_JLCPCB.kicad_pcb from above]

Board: 2 copper layers, 66.9 x 74.5 mm, 12 parts (0 on the bottom side), 18 nets.

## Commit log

2024-02-26 Initial commit of JLCPCB-specific version.
2024-03-13 Initial commit of Type-C board, without Pico modules.
2024-03-13 Add test points for power supplies and oscillator.
2024-03-15 Ignore log files from KiCAD plugins.
2024-03-16 Update schematic with MPN/LCSC, and update manual BOM.
2024-03-17 First round of production cleanup.
2024-03-17 Add decoupling caps for oscillators.
2024-03-17 More improvements:
    * Used different GPIOs for the device USB so the traces can be kept
    away from the 12MHz oscillator circuit.
    * Increased size of VBUS traces so that 1.5A@5V can be safely carried
    from the input connectors to the output connectors.
    * Various minor tweaks.
2024-03-18 Make changes needed to get 3-D model working properly.
2024-03-18 Relocate various items to improve silkscreen placement.
2024-03-18 Adjust mounting hole positions to match original board.
2024-03-19 Use better net labels for UART links.
2024-03-23 Lots of improvements:
    * Modified footprint for USB Type-C connector to use an NPTH for the
    plastic locator pins.
    * Connected USB SHIELD to GND as required by the USB spec.
    * Simplified trace routing and eliminated most vias.
    * Improved VUSB trace routing and sizing.
2024-03-23 Switch to a smaller pushbutton (similar to the one on the Pico)
    Edit imported symbols to use 'LCSC' instead of 'LCSC Part' field name
2024-04-14 Configuration cleanup:
    * Rename 'default_config' to 'user_config' since it includes user-specified configuration
    * Move config_t declaration, and supporting enums/etc., to config.h
    * Remove unused members from config_t
    * Ensure that all members of config_t and other structures have specifed-size types,
    and types that are not any larger than necessary to hold their values
    * Rename NUM_SCREENS to NUM_OUTPUTS since the firmware now supports multiple screens
2024-04-14 Add minIni - a compact INI-file read/write library.
2024-04-21 Add 'cfgtool' for INI-file management of configuration

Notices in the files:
pcb/DeskHop-C-JLCPCB.kicad_pcb:
License: GPL-3.0-only
